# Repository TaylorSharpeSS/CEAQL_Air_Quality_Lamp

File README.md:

# CEAQL_Air_Quality_Lamp
Firmware, EAGLE files and instructions for producing and assembling the Collaboratively Engineered Air Quality Lamp - A project developed by Autodesk and SweetSense

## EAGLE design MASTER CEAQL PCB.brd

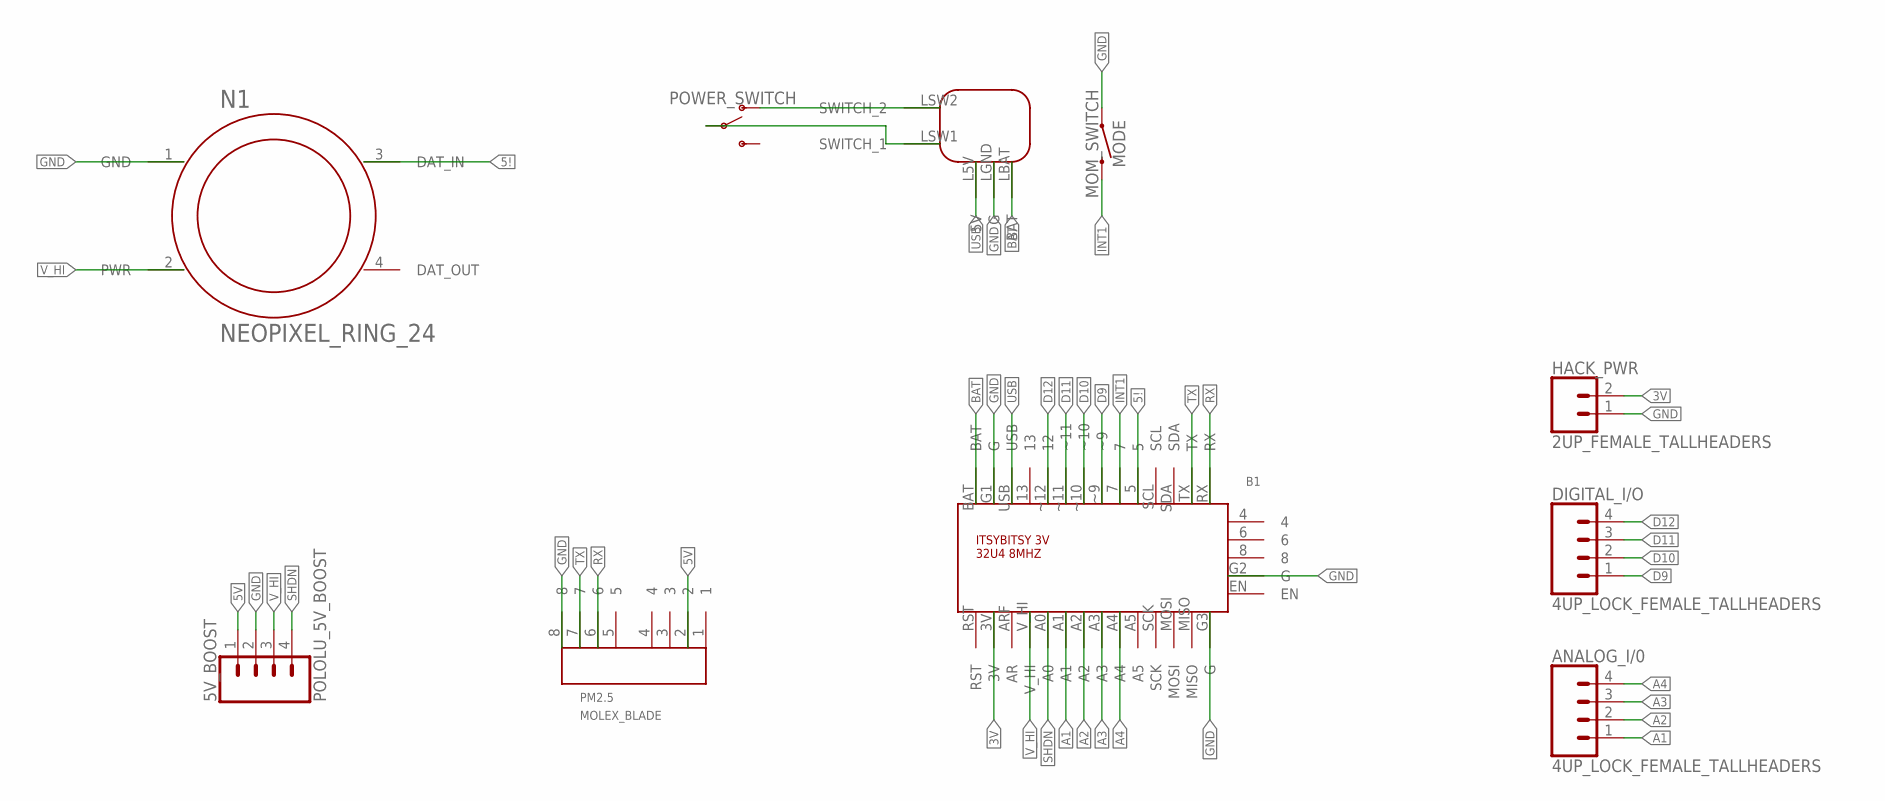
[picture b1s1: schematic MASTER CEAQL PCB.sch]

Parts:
5V_BOOST: POLOLU_5V_BOOST; POLOLU_5V_HEADERS
ANALOG_I/0: 4UP_LOCK_FEMALE_TALLHEADERS; 1X04_LOCK_TALL
B1: ITSY_BITSY
DIGITAL_I/O: 4UP_LOCK_FEMALE_TALLHEADERS; 1X04_LOCK_TALL
HACK_PWR: 2UP_FEMALE_TALLHEADERS; 1X02
L1: LIPOLY_CHARGER
MODE: MOM_SWITCH; TACTILE_SWITCH_PTH_6.0MM
N1: NEOPIXEL_RING_24; NEOPIXEL_RNG_24
PM2.5: MOLEX_BLADE; 53047-08
POWER_SWITCH: SWITCH_SPDT_PINMOUNT; SWITCH_SPDT_PTH_11.6X4.0MM_LOCK

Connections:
3V: B1.3V, HACK_PWR.2
5!: B1.5, N1.3 (DAT_IN)
5V: 5V_BOOST.1, PM2.5.2
A1: ANALOG_I/0.1, B1.A1
A2: ANALOG_I/0.2, B1.A2
A3: ANALOG_I/0.3, B1.A3
A4: ANALOG_I/0.4, B1.A4
BAT: B1.BAT, L1.LBAT (BAT)
D9: B1.~9, DIGITAL_I/O.1
D10: B1.~10, DIGITAL_I/O.2
D11: B1.~11, DIGITAL_I/O.3
D12: B1.~12 (12), DIGITAL_I/O.4
GND: 5V_BOOST.2, B1.G1 (G), B1.G2 (G), B1.G3 (G), HACK_PWR.1, L1.LGND (G), MODE.1, N1.1 (GND), PM2.5.8
INT1: B1.7, MODE.2
unnamed: L1.LSW2 (SWITCH_2), POWER_SWITCH.1 (O)
unnamed: L1.LSW1 (SWITCH_1), POWER_SWITCH.2
RX: B1.RX, PM2.5.6
SHDN: 5V_BOOST.4, B1.A0
TX: B1.TX, PM2.5.7
USB: B1.USB, L1.L5V (5V)
V_HI: 5V_BOOST.3, B1.V_HI, N1.2 (PWR)

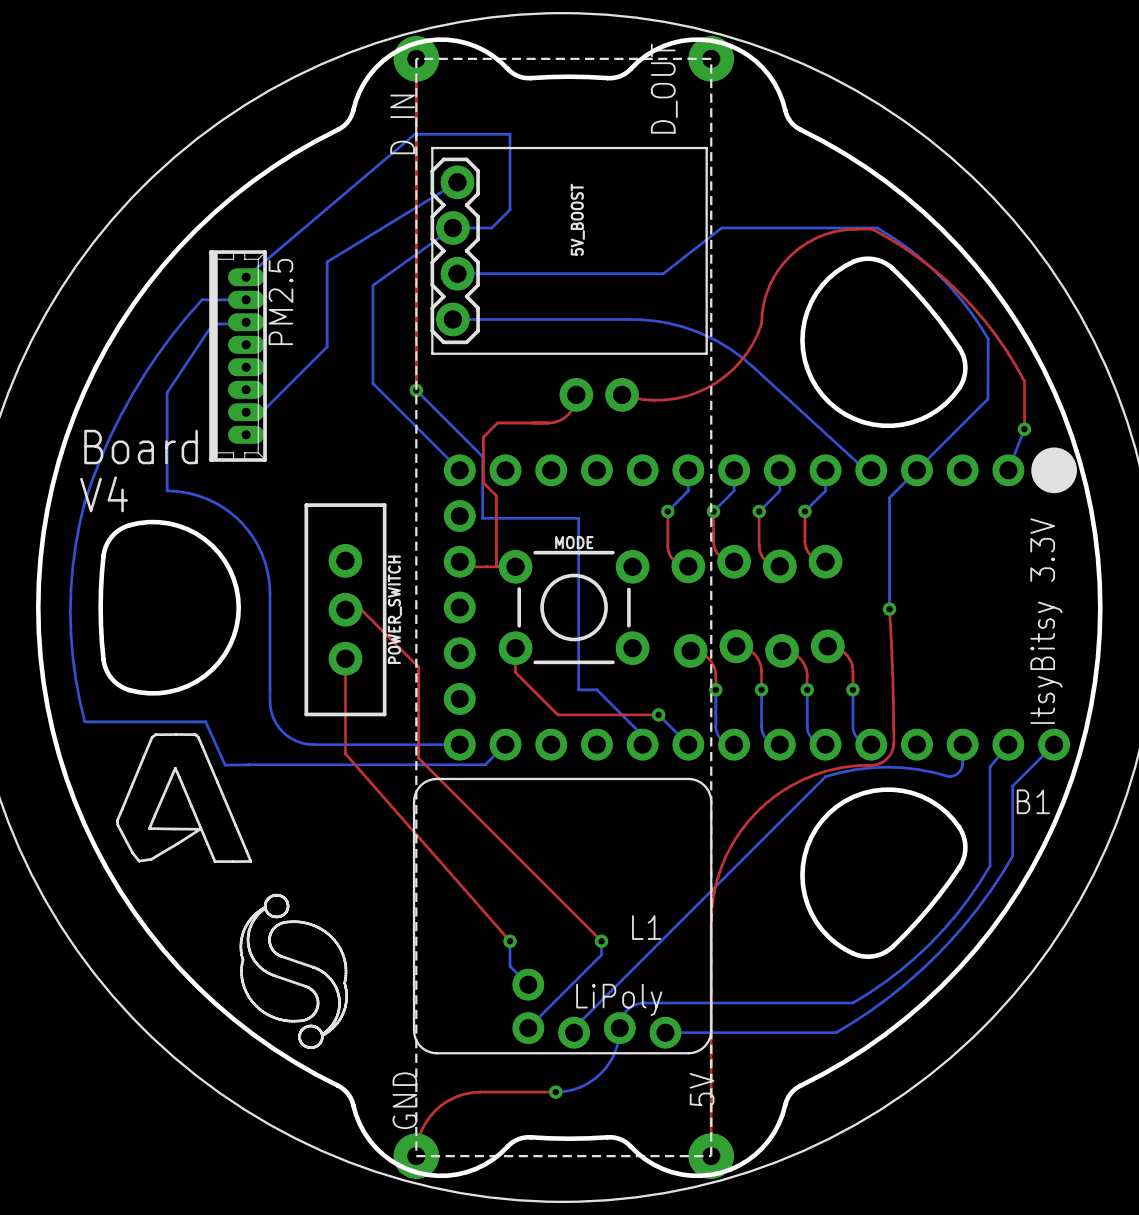
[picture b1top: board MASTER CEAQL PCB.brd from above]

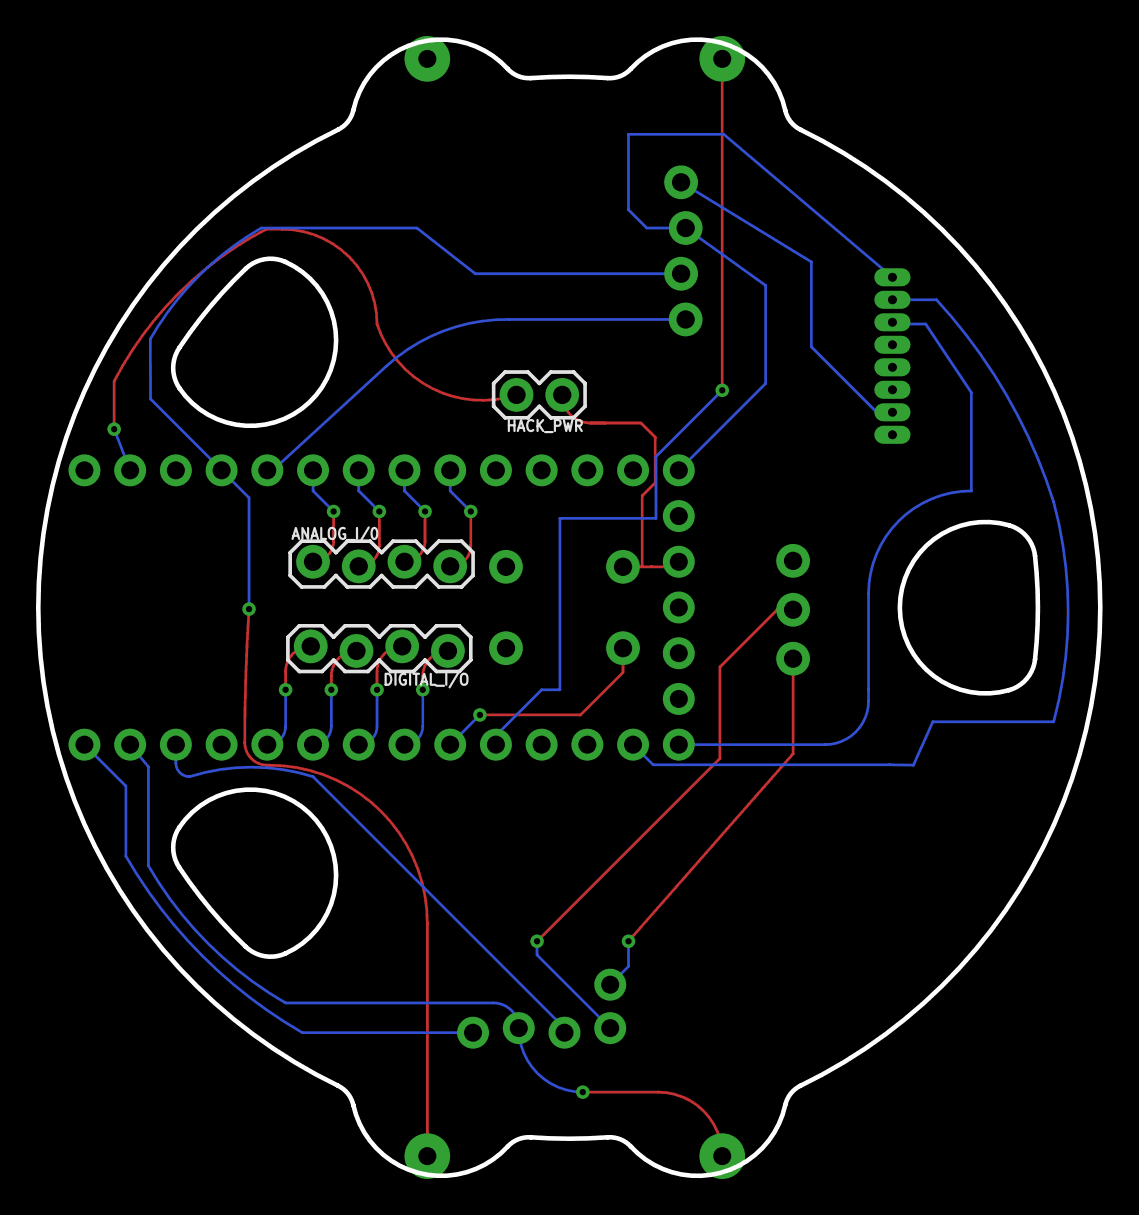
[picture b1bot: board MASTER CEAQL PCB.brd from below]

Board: 2 copper layers, 59.0 x 63.1 mm, 10 parts (3 on the bottom side), 21 nets.

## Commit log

2019-01-07 Add files via upload
    To manufacture your own CEAQL, you'll need a soldering station for through-hole components.
    (1) Order parts from the CEAQL BOM. The BOM includes a link to a public PCB which can be ordered through OSH Park.
    (2) 3D print or machine the mechanical components based on the Fusion 360 design, which you can download here: https://www.autodesk.com/campaigns/concept-to-production
    (3) Follow the soldering work instructions included in this repository.
    (4) Install the modified HPMA library through the Arduino IDE. Upload the V7 firmware to your board through the Arduino IDE.
    (5) Assemble the sensor, turn it on, and test your air quality!
2019-06-07 3D Printable CEAQL Parts
    STL files to produce the mechanical components of the CEAQL. All of these parts can be printed on a standard 3D printer without needing support material. Suggested layer height is 0.10mm.
2019-10-07 Added fasteners (6-32 x 3") to BOM
